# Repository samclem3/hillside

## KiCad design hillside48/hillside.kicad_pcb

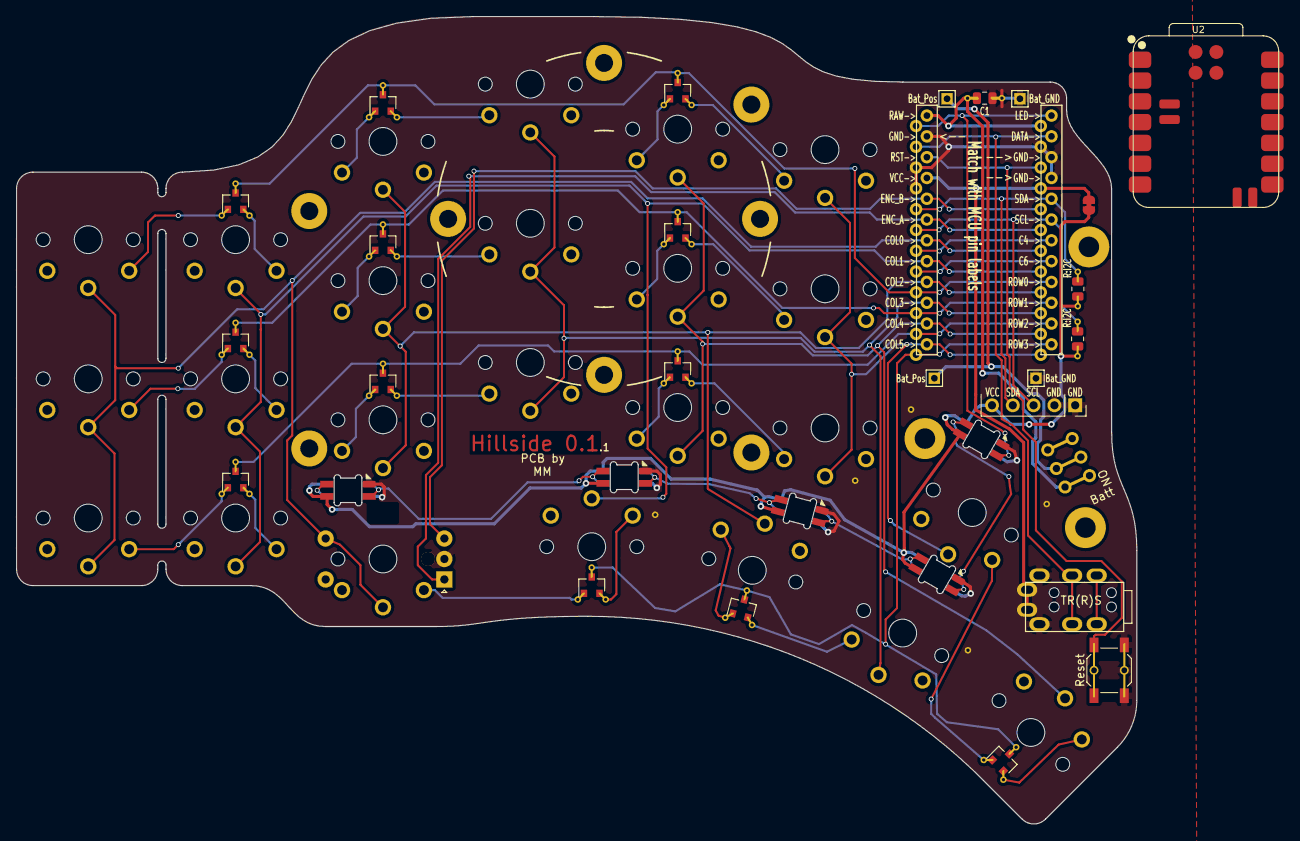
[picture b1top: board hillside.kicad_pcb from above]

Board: 2 copper layers, 136.8 x 98.6 mm, 66 parts (0 on the bottom side), 50 nets.

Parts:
C1: 4u7; C_0805_2012Metric
D1, D2, D3, D4, D5: SK6812-MINI-E
D7, D8, D9, D10, D11, D12, D13, D14, D15, D16, D17, D18: BAV70; SOT-23
H1: Mount_Tenting; Tenting_Puck
H2: Trackball; Pimoroni_Trackball
H4, H5, H6, H7: MountHole; MountingHole_2.2mm_M2_Pad
J1: Haptic; Pimoroni_Haptic
J2: TRRS; MJ-4PP-9
J3, J5: Bat_Pos; 1pin_conn
J4, J6: Bat_GND; 1pin_conn
JP1: VccJumper; SolderJumper-2_P1.3mm_Bridged_RoundedPad1.0x1.5mm
K1, K2, K3, K4, K5, K6, K7, K8, K9, K10, K11, K12, K13, K14, K15, K16, K17, K18, K19, K21, K22, K23, K24: SW_Key; pg1350-R
K20: SW_Rotary; pg1350-DR_rotary
R1, R2: R:I2C; R_0805_2012Metric
SW1: Reset; SW_SPST_SKQG_WithStem
SW2: SW_Power; SW_SPDT_JS202011AQN
U1: ProMicro_r; ProMicro_v2
U2: XIAO-nRF52840-SMD
V1, V2, V3, V4, V5: Via; VIA-0.8mm

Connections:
GND: C1.2, D1.3 (VSS), D2.3 (VSS), D3.3 (VSS), D4.3 (VSS), D5.3 (VSS), J1.1, J1.2, J2.T (Tip), J4.1 (Pin_1_1), J6.1 (Pin_1_1), K20.C, SW1.2, U1.3 (GND), U1.4 (GND), U1.23 (GND), V1.1 (via_1), V2.1 (via_1), V3.1 (via_1), V4.1 (via_1), V5.1 (via_1)
LED: D1.4 (DIN), U1.1 (D3/TX0)
unnamed: D1.2 (DOUT), D2.4 (DIN)
unnamed: D2.2 (DOUT), D3.4 (DIN)
unnamed: D3.2 (DOUT), D4.4 (DIN)
unnamed: D4.2 (DOUT), D5.4 (DIN)
unnamed: D7.1 (A1), K1.2
unnamed: D7.2 (A2), K2.2
unnamed: D8.1 (A1), K3.2
unnamed: D8.2 (A2), K4.2
unnamed: D9.1 (A1), K5.2
unnamed: D9.2 (A2), K6.2
unnamed: D10.1 (A1), K7.2
unnamed: D10.2 (A2), K8.2
unnamed: D11.1 (A1), K9.2
unnamed: D11.2 (A2), K10.2
unnamed: D12.1 (A1), K11.2
unnamed: D12.2 (A2), K12.2
unnamed: D13.1 (A1), K13.2
unnamed: D13.2 (A2), K14.2
unnamed: D14.1 (A1), K15.2
unnamed: D14.2 (A2), K16.2
unnamed: D15.1 (A1), K17.2
unnamed: D15.2 (A2), K18.2
unnamed: D16.1 (A1), K20.S2
unnamed: D16.2 (A2), K21.2
unnamed: D17.1 (A1), K22.2
unnamed: D17.2 (A2), K23.2
unnamed: D18.1 (A1), K19.2
unnamed: D18.2 (A2), K24.2
SCL: J1.3, R1.2, U1.6 (SCL/D0/3)
SDA: J1.4, R2.2, U1.5 (SDA/D1/2)
VCC: J2.S (Sleeve), JP1.1 (A), U1.21 (VCC)
VCC_ACC: D1.1 (VDD), D2.1 (VDD), D3.1 (VDD), D4.1 (VDD), D5.1 (VDD), J1.5, JP1.2 (B), R1.1, R2.1
bat+: J3.1 (Pin_1_1), J5.1 (Pin_1_1), SW2.2 (B)
col0: K1.1, K7.1, K13.1, K20.S1, U1.18 (A1/F6)
col1: K2.1, K8.1, K14.1, K21.1, U1.17 (A0/F7)
col2: K3.1, K9.1, K15.1, K22.1, U1.16 (15/B1)
col3: K4.1, K10.1, K16.1, K23.1, U1.15 (14/B3)
col4: K5.1, K11.1, K17.1, K24.1, U1.14 (16/B2)
col5: K6.1, K12.1, K18.1, K19.1, U1.13 (10/B6)
data: J2.R1 (Ring1), U1.2 (D2/RX1)
enc_a: K20.A, U1.19 (A2/F5)
enc_b: K20.B, U1.20 (A3/F4)
raw: C1.1, SW2.3 (C), U1.24 (RAW)
reset: SW1.1, U1.22 (RST)
row0: D7.3 (K), D8.3 (K), D9.3 (K), U1.9 (D7/6)
row1: D10.3 (K), D11.3 (K), D12.3 (K), U1.10 (E6/7)
row2: D13.3 (K), D14.3 (K), D15.3 (K), U1.11 (B4/8)
row3: D16.3 (K), D17.3 (K), D18.3 (K), U1.12 (B5/9)
